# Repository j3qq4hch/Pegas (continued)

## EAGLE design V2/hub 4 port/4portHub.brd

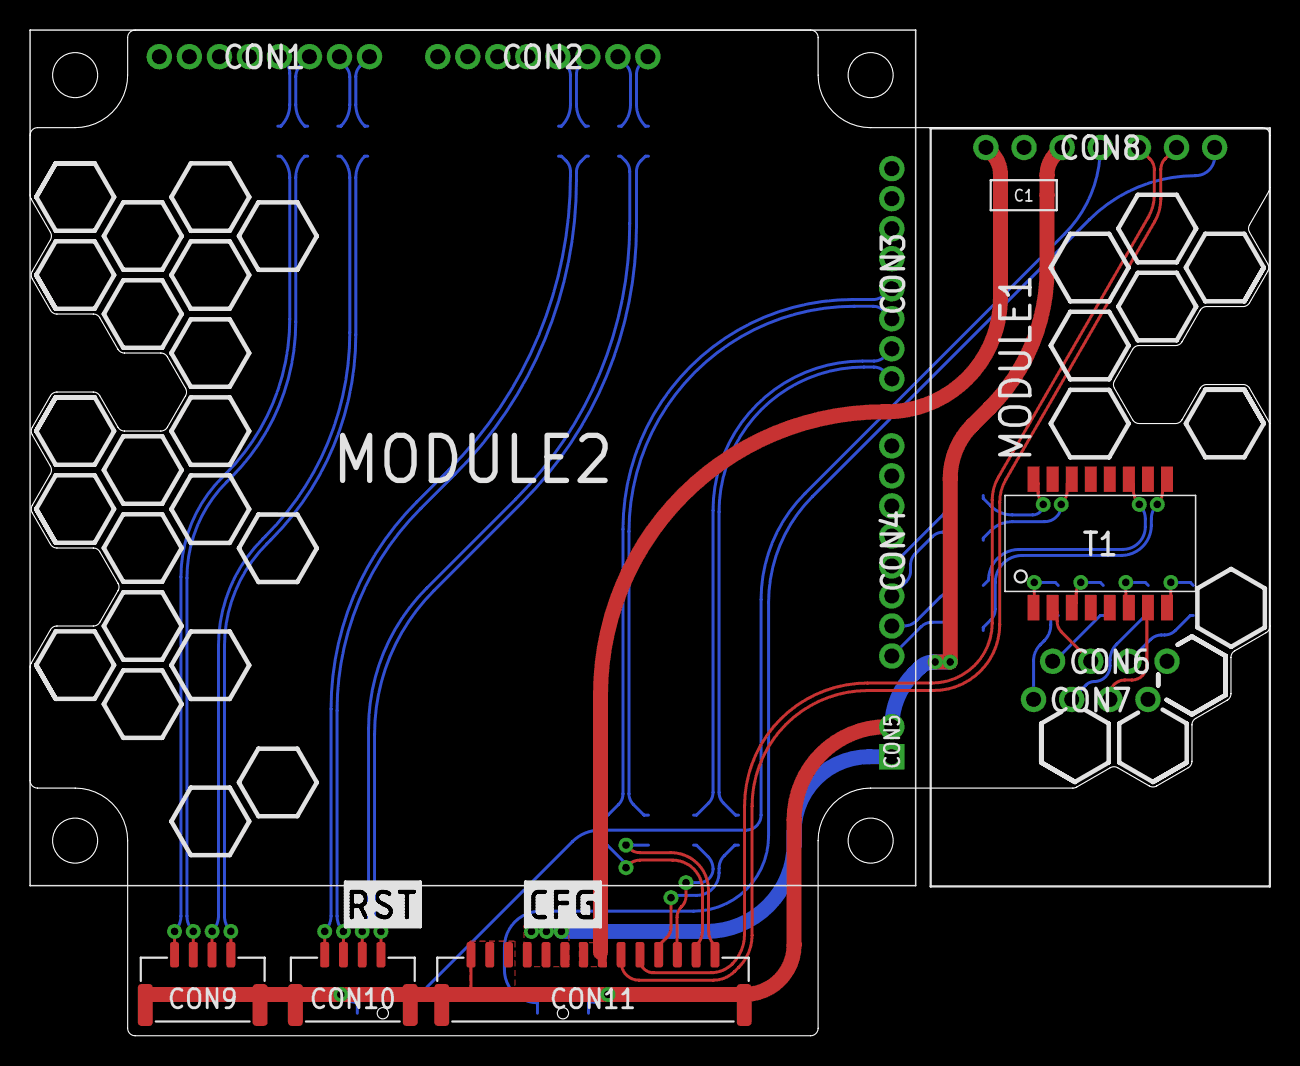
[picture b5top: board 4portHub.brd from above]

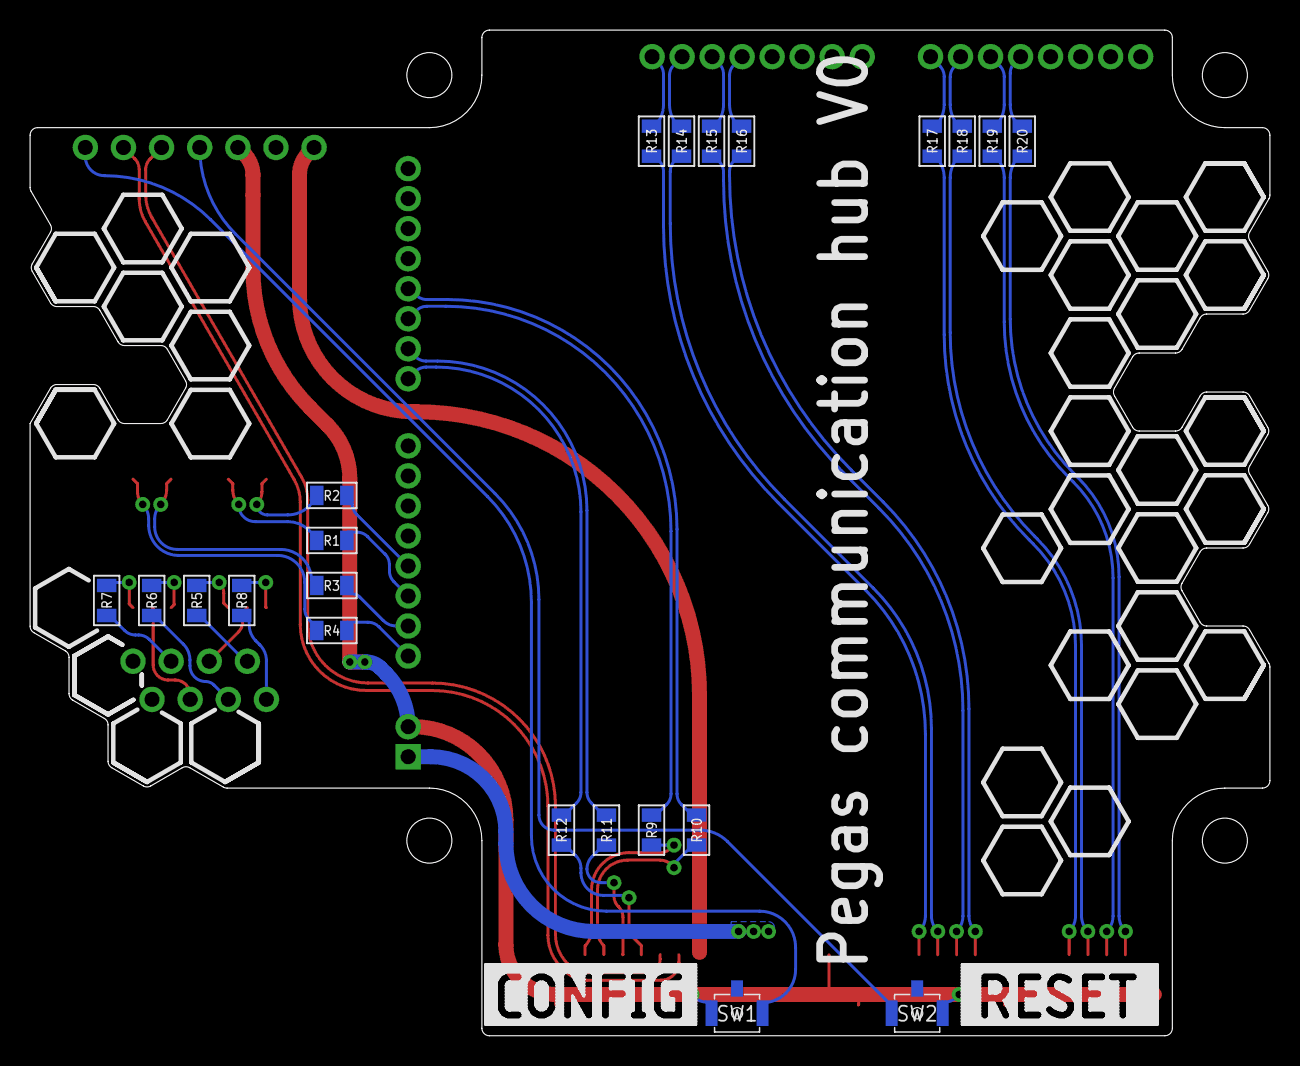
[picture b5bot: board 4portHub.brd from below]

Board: 2 copper layers, 82.6 x 67.0 mm, 29 parts (22 on the bottom side), 49 nets.

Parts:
C1: 10uF; C1206
CON9, CON10: CON-4P-TABS-JST-GH-TOP; BM04B-GHS-TB
CON11: CON-14P-TABS-JST-GH-TOP; BM14B-GHS-TBT
MODULE1: USR-TCP232-T2
MODULE2: ANDDEAR_4PORT2
R1, R2, R3, R4, R5, R6, R7, R8, R9, R10, R11, R12, R13, R14, R15, R16, R17, R18, R19, R20: 000; R0805
SW1, SW2: TACT_SWITCH-B3U-3100P(M)-B; B3U-3100P(M)-B
T1: H1102NL; H1102

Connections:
CFG: MODULE1.CFG, SW1.P$1
ETH_RX+: CON11.2, R10.1
ETH_RX-: CON11.1, R9.1
ETH_TX+: CON11.4, R12.1
ETH_TX-: CON11.3, R11.1
ETH_UART_RX: CON11.6, MODULE1.RXD
ETH_UART_TX: CON11.5, MODULE1.TXD
GND: C1.P$1, CON9.M$0, CON9.M$1, CON10.M$0, CON10.M$1, CON11.12, CON11.13, CON11.14, CON11.M$0, CON11.M$1, MODULE1.GND, MODULE2.GND, SW1.P$2, SW2.P$1
unnamed: R7.2, T1.8
unnamed: R6.2, T1.6
unnamed: R5.2, T1.3
unnamed: R8.2, T1.1
unnamed: R4.1, T1.9
unnamed: R3.1, T1.11
unnamed: R1.1, T1.14
unnamed: R2.1, T1.16
unnamed: MODULE2.J2.1, R4.2
unnamed: MODULE2.J2.2, R3.2
unnamed: MODULE2.J2.3, R1.2
unnamed: MODULE2.J2.4, R2.2
unnamed: MODULE1.J6, R7.1
unnamed: MODULE1.J1, R8.1
unnamed: MODULE1.J2, R5.1
unnamed: MODULE1.J3, R6.1
unnamed: MODULE2.J3.3, R9.2
unnamed: MODULE2.J3.4, R10.2
unnamed: MODULE2.J3.2, R11.2
unnamed: MODULE2.J3.1, R12.2
unnamed: CON9.1, R17.2
unnamed: CON9.2, R18.2
unnamed: CON9.3, R19.2
unnamed: CON9.4, R20.2
unnamed: CON10.1, R13.2
unnamed: CON10.2, R14.2
unnamed: CON10.3, R15.2
unnamed: CON10.4, R16.2
unnamed: MODULE2.J4.1, R13.1
unnamed: MODULE2.J4.2, R14.1
unnamed: MODULE2.J4.3, R15.1
unnamed: MODULE2.J4.4, R16.1
unnamed: MODULE2.J5.1, R17.1
unnamed: MODULE2.J5.2, R18.1
unnamed: MODULE2.J5.3, R19.1
unnamed: MODULE2.J5.4, R20.1
unnamed: MODULE1.J5, T1.7
unnamed: MODULE1.J4, T1.2
RST: MODULE1.RST, SW2.P$2
VDD_5V: C1.P$2, CON11.7, CON11.8, MODULE1.5V
VDD_12V: CON11.9, CON11.10, CON11.11, MODULE2.SUP

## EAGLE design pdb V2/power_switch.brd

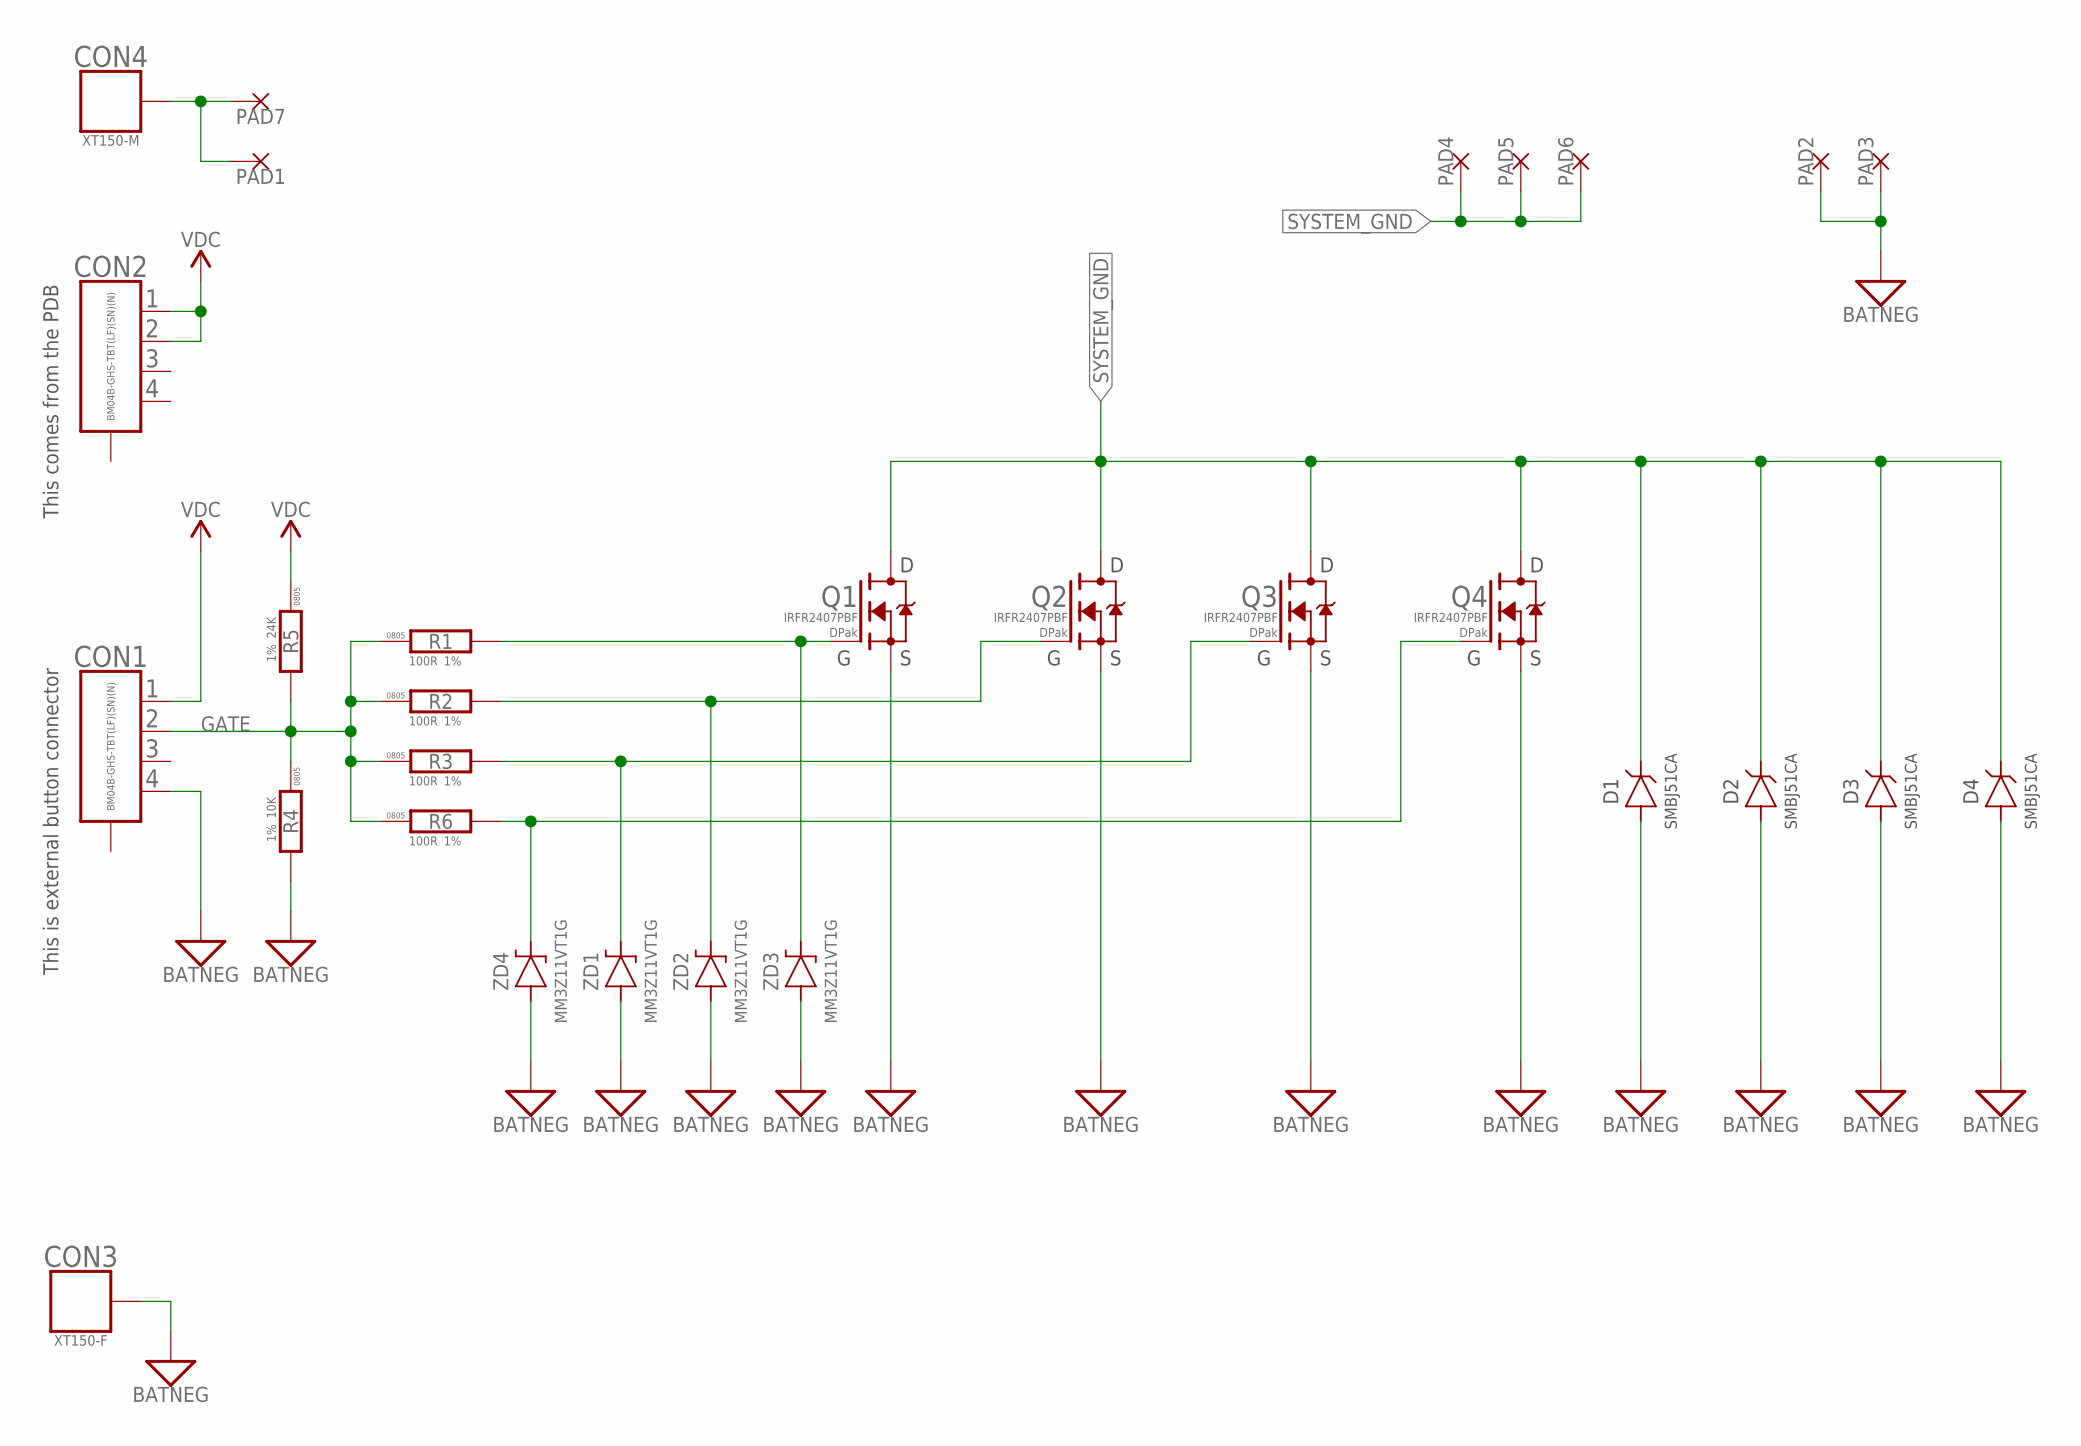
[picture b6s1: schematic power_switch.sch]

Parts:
CON1, CON2: CON-4P-TABS-JST-GH-TOP; BM04B-GHS-TB
CON3: CON-1P-XT150-FEMALE-PIN; XT150-FEMALE-PIN
CON4: CON-1P-XT150-MALE-PIN; XT150-MALE-PIN
D1, D2, D3, D4: SMBJ51CA-SMB; DO-214AA(SMB)
PAD1, PAD2, PAD3, PAD4, PAD5, PAD6, PAD7: PAD-5X8; 5X8
Q1, Q2, Q3, Q4: IRFR2407PBF; D-PAK
R1, R2, R3, R6: 100R; R0805
R4: 10K; R0805
R5: 24K; R0805
ZD1, ZD2, ZD3, ZD4: MM3Z11V; SOD323

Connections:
BATNEG: CON1.4, CON3.P$1, D1.A, D2.A, D3.A, D4.A, PAD2.P$1, PAD3.P$1, Q1.S, Q2.S, Q3.S, Q4.S, R4.2, ZD1.A, ZD2.A, ZD3.A, ZD4.A
BAT_POSITIVE: CON4.P$1, PAD1.P$1, PAD7.P$1
GATE: CON1.2, R1.1, R2.1, R3.1, R4.1, R5.2, R6.1
unnamed: Q2.G, R2.2, ZD2.C
unnamed: Q3.G, R3.2, ZD1.C
unnamed: Q1.G, R1.2, ZD3.C
unnamed: Q4.G, R6.2, ZD4.C
SYSTEM_GND: D1.C, D2.C, D3.C, D4.C, PAD4.P$1, PAD5.P$1, PAD6.P$1, Q1.D, Q2.D, Q3.D, Q4.D
VDC: CON1.1, CON2.1, CON2.2, R5.1

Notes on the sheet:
This comes from the PDB
This is external button connector

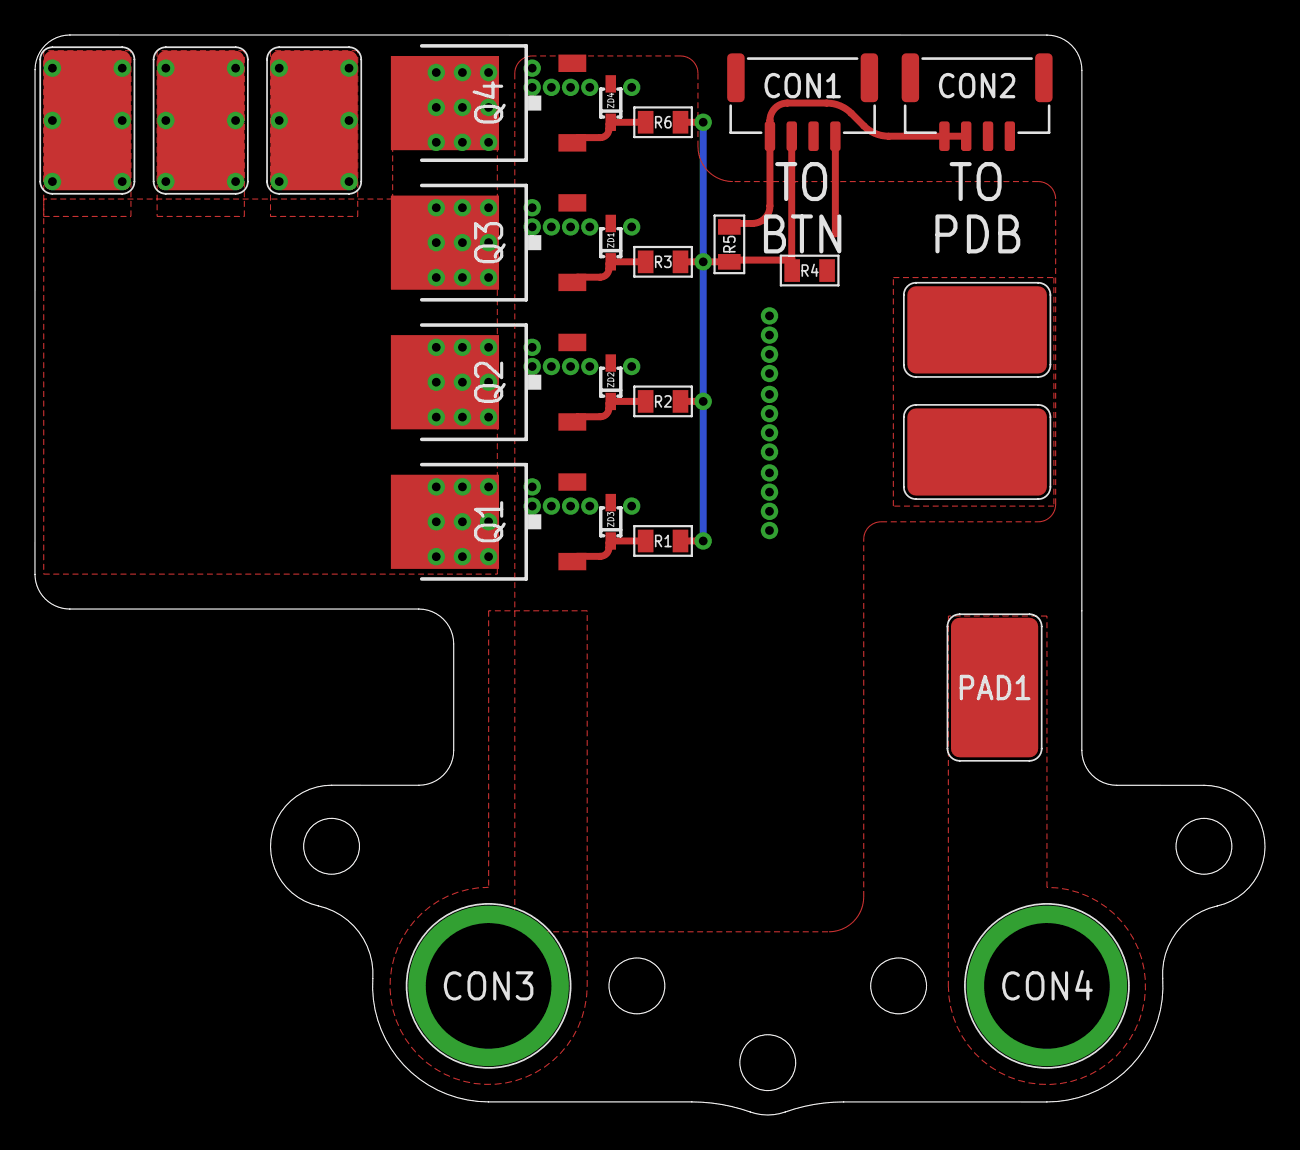
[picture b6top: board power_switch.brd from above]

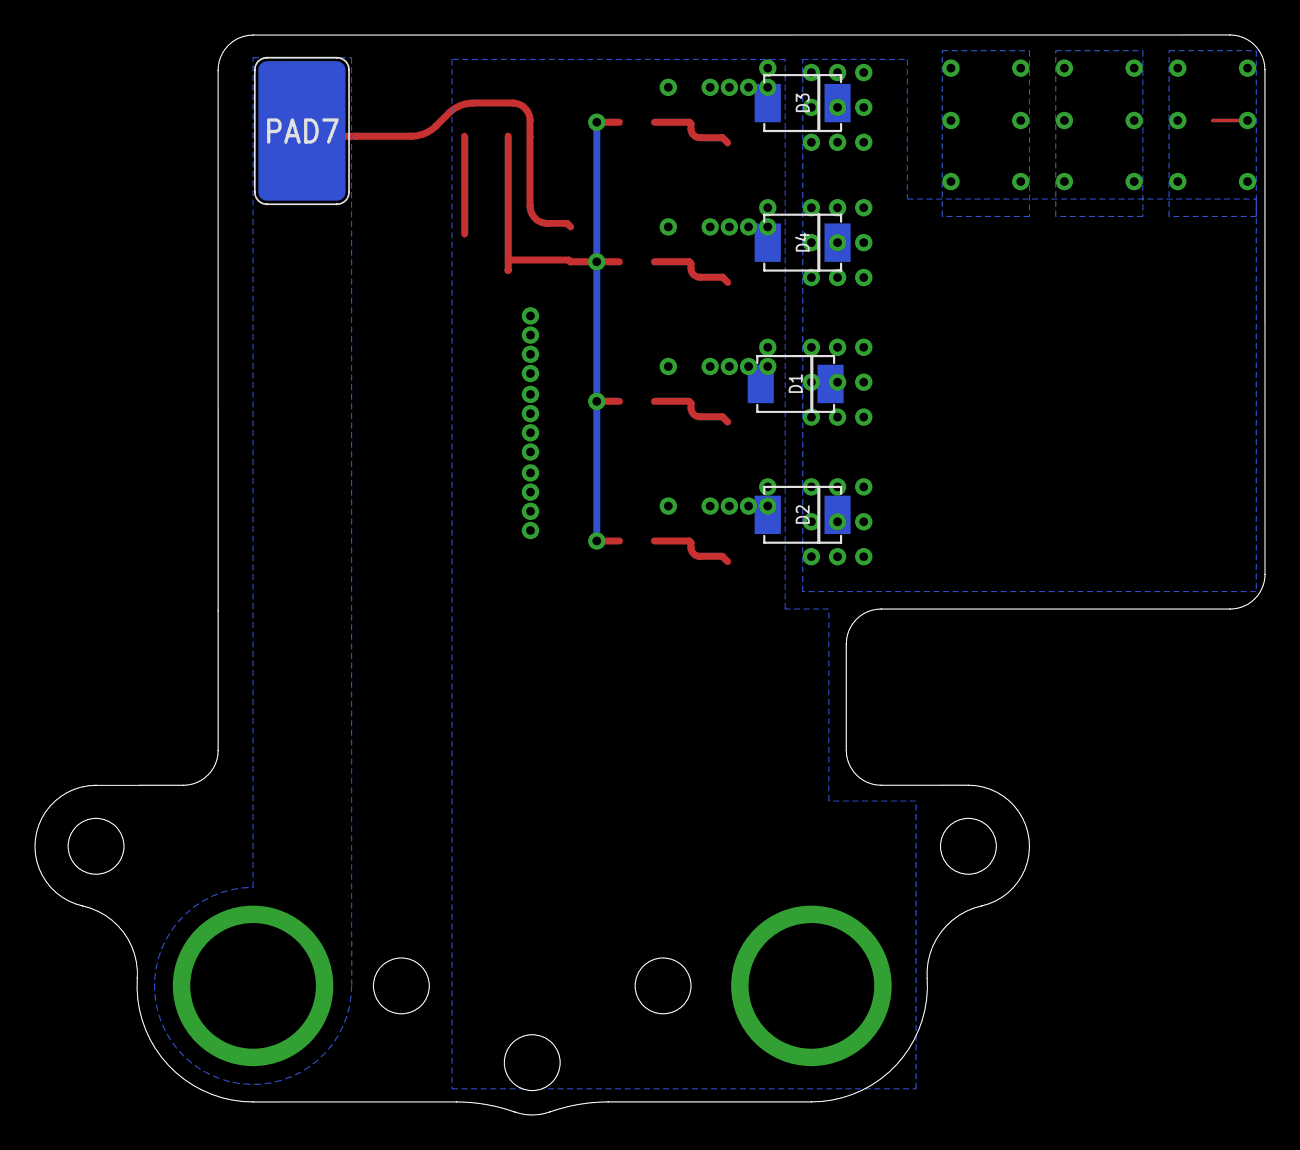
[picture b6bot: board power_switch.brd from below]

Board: 2 copper layers, 70.5 x 61.9 mm, 29 parts (5 on the bottom side), 9 nets.

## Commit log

2022-12-02 initial import
2022-12-02 manf docs import
2022-12-06 readme update
2022-12-19 V3 import
2022-12-19 blah
2022-12-20 updates for V3
2022-12-20 silkscreen updates
2022-12-23 V3.1 initial import
2022-12-23 V3 finalization
2022-12-23 V3 finished
2022-12-23 uarts
2022-12-23 link leds added
2022-12-26 Naming
2022-12-26 attribute updates
2022-12-26 Payload connector replaced with 2 6-pin ones
2022-12-27 InterPCB connectors issues fix
2022-12-27 silk updates
2022-12-28 Minor fixes here and there
2022-12-30 PowerPCB updated for compatibility with rezonit requerements
2023-01-08 readme
